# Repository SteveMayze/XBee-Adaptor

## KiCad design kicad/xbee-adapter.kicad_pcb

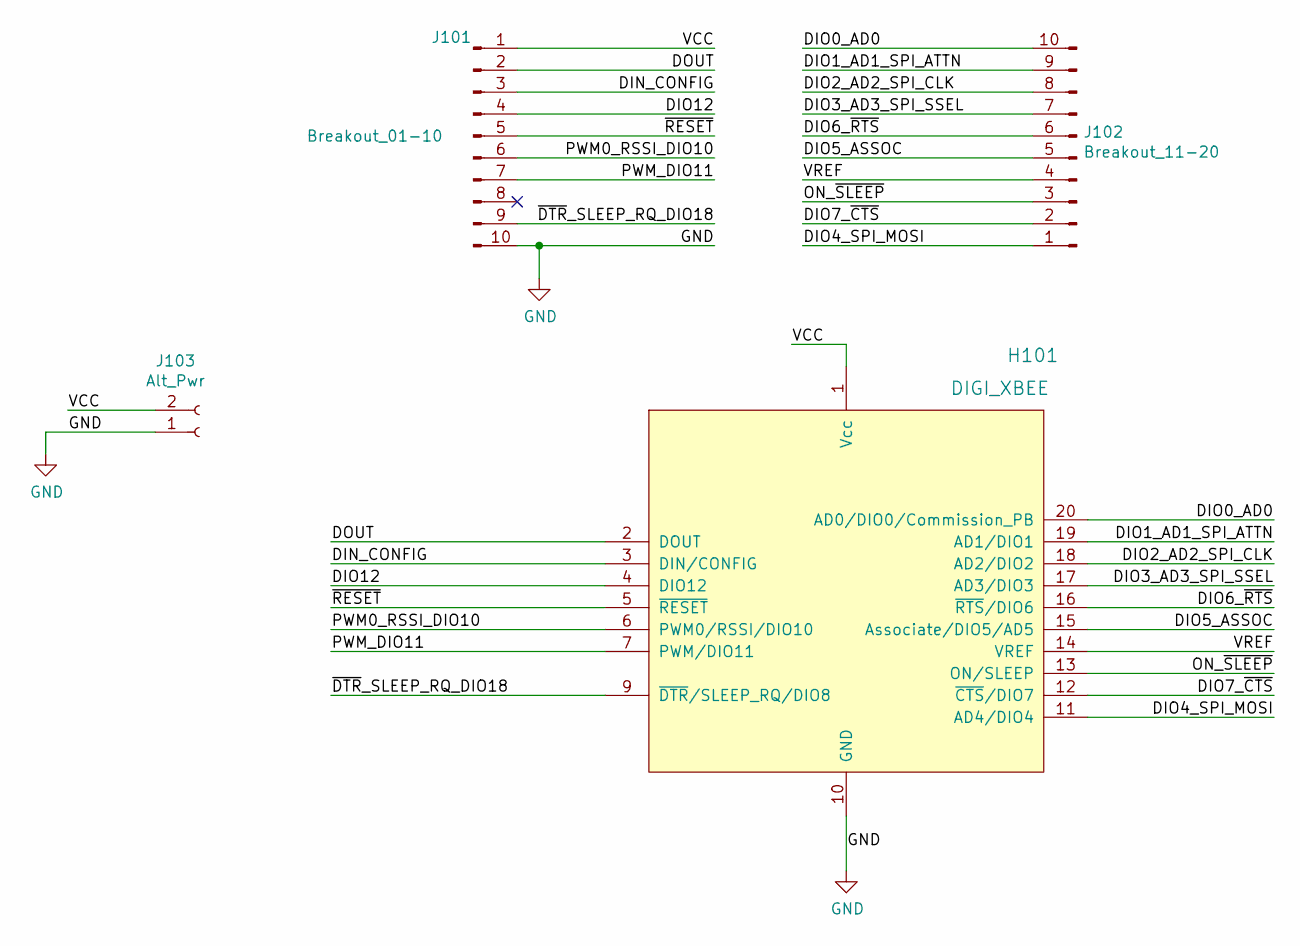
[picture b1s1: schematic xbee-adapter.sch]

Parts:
H101: DIGI_XBEE; XBEE_S2C
J101: Breakout_01-10; Pin_Header_Straight_1x10_Pitch2.54mm
J102: Breakout_11-20; Pin_Header_Straight_1x10_Pitch2.54mm
J103: Alt_Pwr; Socket_Strip_Straight_1x02_Pitch2.54mm

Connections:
/DIN_CONFIG: H101.3 (DIN/CONFIG), J101.3
/DIO0_AD0: H101.20 (AD0/DIO0/Commission_PB), J102.10
/DIO1_AD1_SPI_ATTN: H101.19 (AD1/DIO1), J102.9
/DIO2_AD2_SPI_CLK: H101.18 (AD2/DIO2), J102.8
/DIO3_AD3_SPI_SSEL: H101.17 (AD3/DIO3), J102.7
/DIO4_SPI_MOSI: H101.11 (AD4/DIO4), J102.1
/DIO5_ASSOC: H101.15 (Associate/DIO5/AD5), J102.5
/DIO6_~RTS: H101.16 (~RTS~/DIO6), J102.6
/DIO7_~CTS: H101.12 (~CTS~/DIO7), J102.2
/DIO12: H101.4 (DIO12), J101.4
/DOUT: H101.2 (DOUT), J101.2
/ON_~SLEEP: H101.13 (ON/SLEEP), J102.3
/PWM0_RSSI_DIO10: H101.6 (PWM0/RSSI/DIO10), J101.6
/PWM_DIO11: H101.7 (PWM/DIO11), J101.7
/VCC: H101.1 (Vcc), J101.1, J103.2
/VREF: H101.14 (VREF), J102.4
/~DTR~_SLEEP_RQ_DIO18: H101.9 (~DTR~/SLEEP_RQ/DIO8), J101.9
/~RESET: H101.5 (~RESET), J101.5
GND: H101.10 (GND), J101.10, J103.1

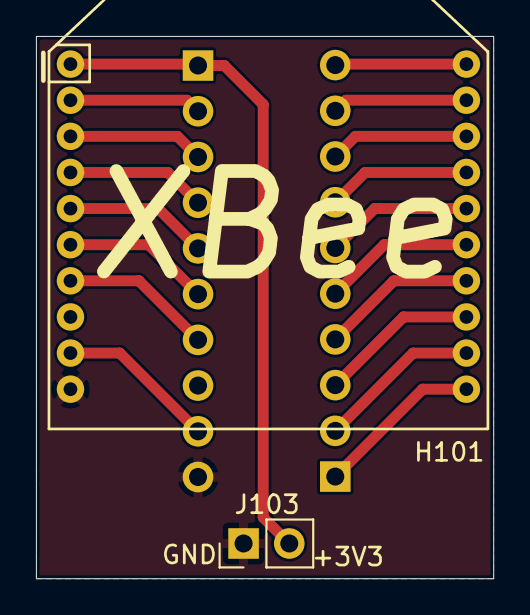
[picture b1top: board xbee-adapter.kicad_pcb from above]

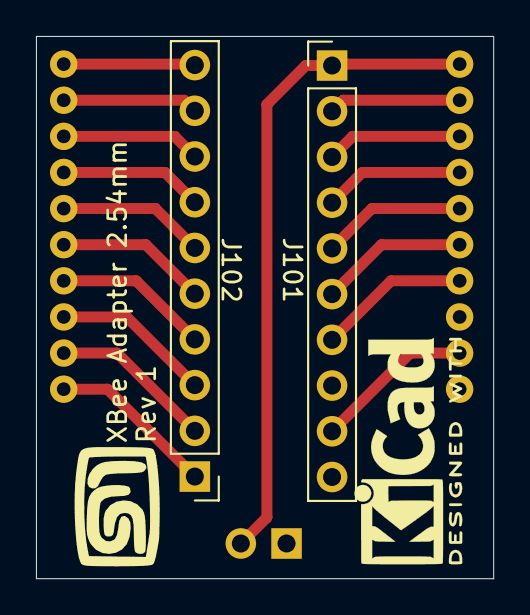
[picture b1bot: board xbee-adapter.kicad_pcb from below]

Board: 2 copper layers, 25.4 x 30.1 mm, 4 parts (2 on the bottom side), 19 nets.

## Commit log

2020-08-02 Initial checkin
